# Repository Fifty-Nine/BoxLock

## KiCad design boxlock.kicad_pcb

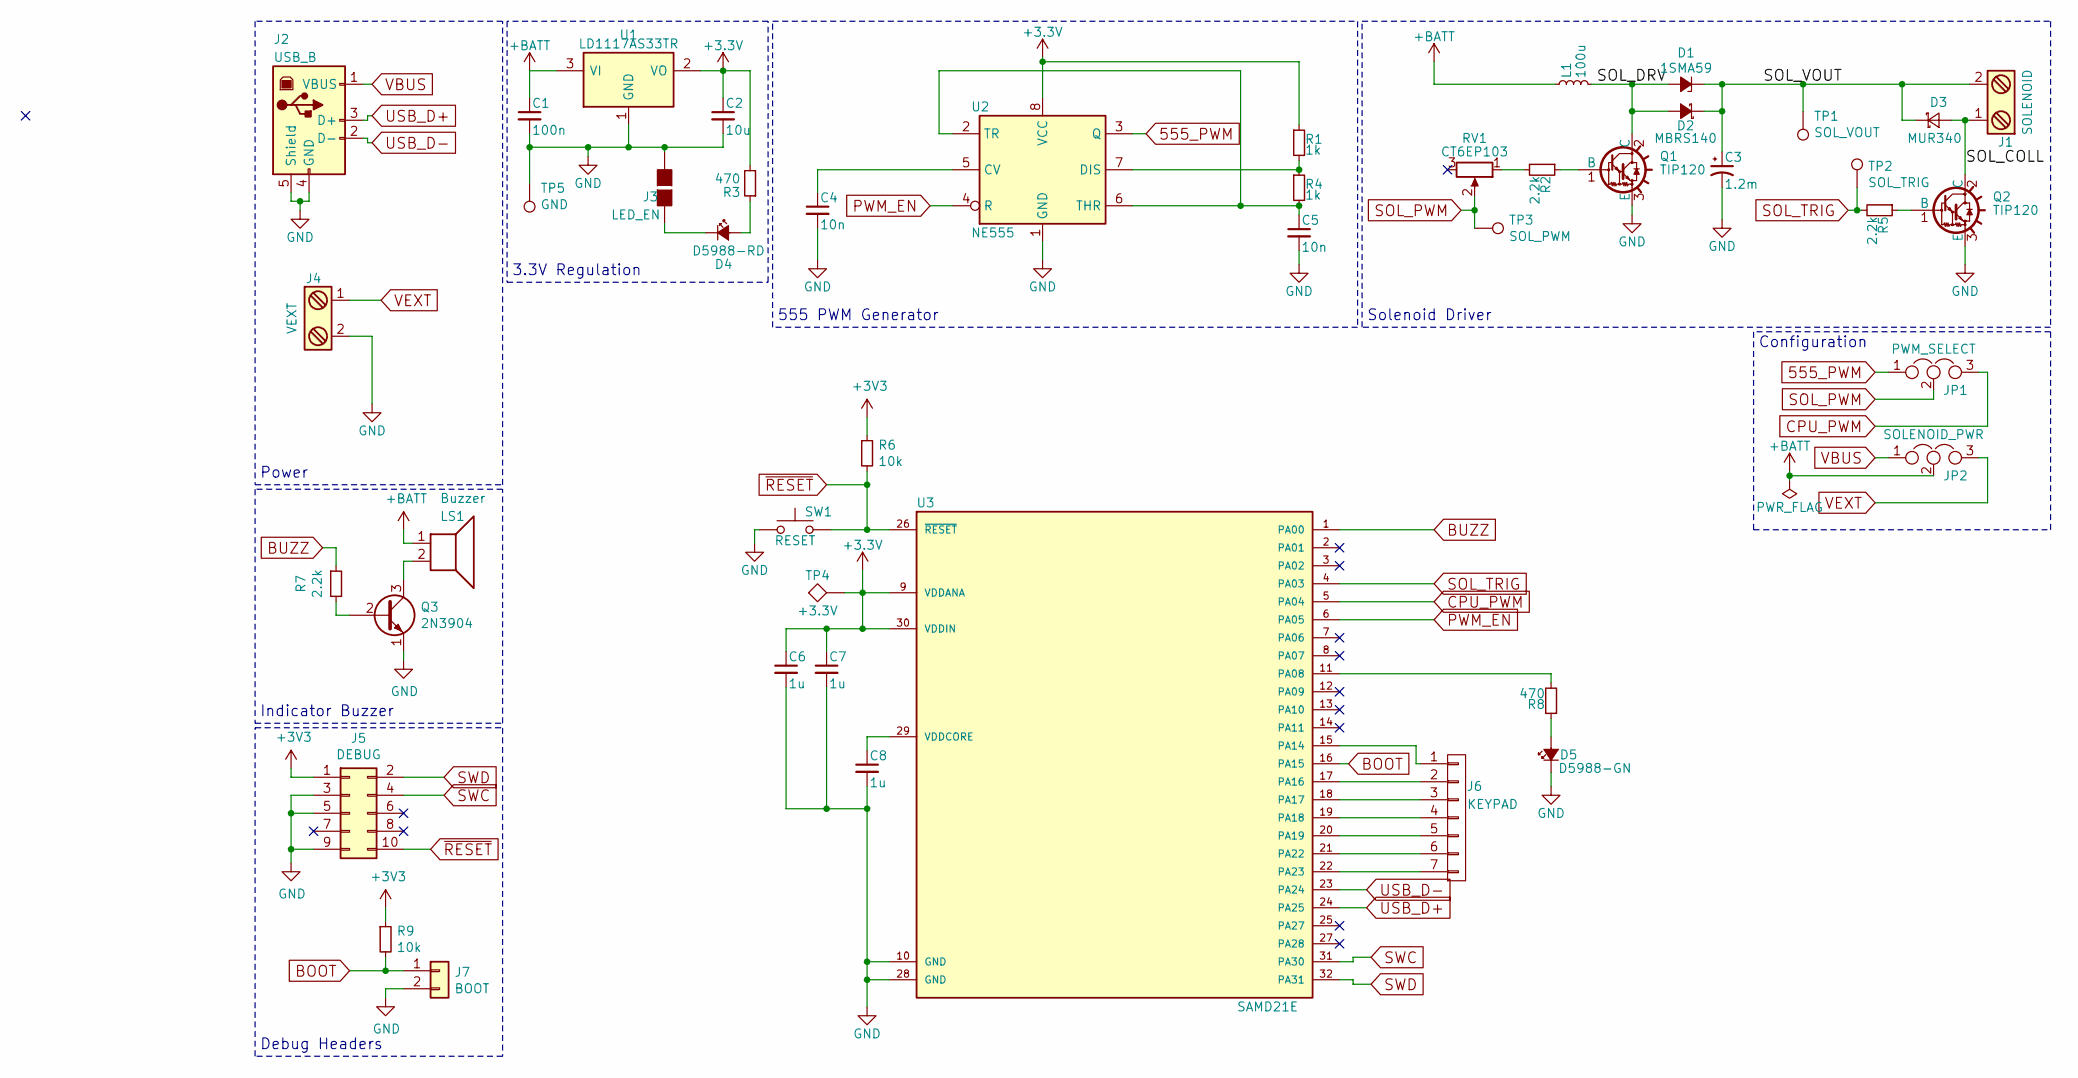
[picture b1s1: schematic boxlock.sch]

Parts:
C1: 100n; C_0805_HandSoldering
C2: 10u; C_0805_HandSoldering
C3: 1.2m; EEV-FK1V152M
C4, C5: 10n; C_0805_HandSoldering
C6, C7, C8: 1u; C_0805_HandSoldering
D1: 1SMA59; D_SMA
D2: MBRS140; D_SMB
D3: MUR340; D_SMB
D4: D5988-RD; LED_0805_HandSoldering
D5: D5988-GN; LED_0805_HandSoldering
J1: SOLENOID; 282836-2
J2: USB_B; USB_Micro-B-circular
J3: LED_EN; GS2
J4: VEXT; 282836-2
J5: DEBUG; Pin_Header_Straight_2x05_Pitch1.27mm
J6: KEYPAD; Pin_Header_Straight_1x07_Pitch2.54mm
J7: BOOT; Pin_Header_Straight_1x02_Pitch2.54mm
JP1: PWM_SELECT; Pin_Header_Straight_1x03_Pitch2.54mm
JP2: SOLENOID_PWR; Pin_Header_Straight_1x03_Pitch2.54mm
L1: 100u; SRN1060-101M
LS1: Buzzer; CEP-2242
Q1, Q2: TIP120; TO-220-3_Horizontal
Q3: 2N3904; TO-92_Molded_Narrow
R1, R4: 1k; R_0805_HandSoldering
R2, R5, R7: 2.2k; R_0805_HandSoldering
R3, R8: 470; R_0805_HandSoldering
R6, R9: 10k; R_0805_HandSoldering
RV1: CT6EP103; 3362P-1-103LF
SW1: RESET; FSMSMTR
TP1: SOL_VOUT; Test_Point_Keystone_5005-5009_Compact
TP2: SOL_TRIG; Test_Point_Keystone_5005-5009_Compact
TP3: SOL_PWM; Test_Point_Keystone_5005-5009_Compact
TP4: +3.3V; Test_Point_Keystone_5005-5009_Compact
TP5: GND; Test_Point_Keystone_5005-5009_Compact
U1: LD1117AS33TR; SOT-223
U2: NE555; SOIC-8_3.9x4.9mm_Pitch1.27mm
U3: SAMD21E; TQFP-32_7x7mm_Pitch0.8mm

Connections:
555_PWM: JP1.1, U2.3 (Q)
+BATT: C1.1, JP2.2, L1.1, LS1.1, U1.3 (VI)
/SOL_COLL: D3.2 (A), J1.1, Q2.2 (C)
/SOL_DRV: D1.2 (A), D2.2 (A), L1.2, Q1.2 (C)
/SOL_VOUT: C3.1, D1.1 (K), D2.1 (K), D3.1 (K), J1.2, TP1.1
BOOT: J7.1, R9.2, U3.16 (PA15)
BUZZ: R7.1, U3.1 (PA00)
CPU_PWM: JP1.3, U3.5 (PA04)
GND: C1.2, C2.2, C3.2, C4.2, C5.2, C6.2, C7.2, C8.2, D5.1 (K), J2.4 (GND), J2.5 (Shield), J3.2 (G2), J4.2, J5.3, J5.5, J5.9, J7.2, Q1.3 (E), Q2.3 (E), Q3.1 (E), SW1.1, TP5.1, U1.1 (GND), U2.1 (GND), U3.10 (GND), U3.28 (GND)
unnamed: C4.1, U2.5 (CV)
unnamed: C5.1, R4.2, U2.2 (TR), U2.6 (THR)
unnamed: C8.1, U3.29 (VDDCORE)
unnamed: D4.1 (K), J3.1 (G1)
unnamed: D4.2 (A), R3.1
unnamed: D5.2 (A), R8.1
unnamed: J6.1, U3.15 (PA14)
unnamed: J6.2, U3.17 (PA16)
unnamed: J6.3, U3.18 (PA17)
unnamed: J6.4, U3.19 (PA18)
unnamed: J6.5, U3.20 (PA19)
unnamed: J6.6, U3.21 (PA22)
unnamed: J6.7, U3.22 (PA23)
unnamed: LS1.2, Q3.3 (C)
unnamed: Q1.1 (B), R2.1
unnamed: Q2.1 (B), R5.1
unnamed: Q3.2 (B), R7.2
unnamed: R1.2, R4.1, U2.7 (DIS)
unnamed: R2.2, RV1.1
unnamed: R8.2, U3.11 (PA08)
PWM_EN: U2.4 (R), U3.6 (PA05)
SOL_PWM: JP1.2, RV1.2, TP3.1
SOL_TRIG: R5.2, TP2.1, U3.4 (PA03)
SWC: J5.4, U3.31 (PA30)
SWD: J5.2, U3.32 (PA31)
USB_D+: J2.3 (D+), U3.24 (PA25)
USB_D-: J2.2 (D-), U3.23 (PA24)
VBUS: J2.1 (VBUS), JP2.1
VEXT: J4.1, JP2.3
~RESET: J5.10, R6.2, SW1.2, U3.26 (~RESET~)

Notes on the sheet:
Solenoid Driver
555 PWM Generator
3.3V Regulation
Configuration
Power
Indicator Buzzer
Debug Headers

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
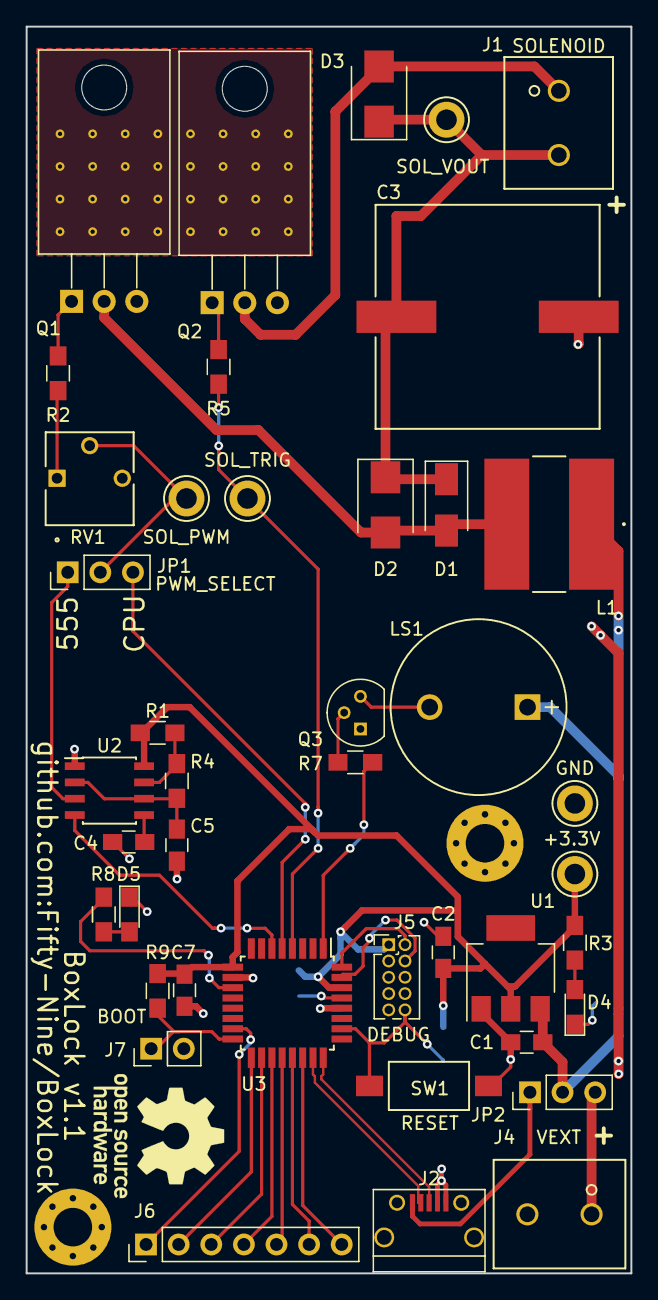
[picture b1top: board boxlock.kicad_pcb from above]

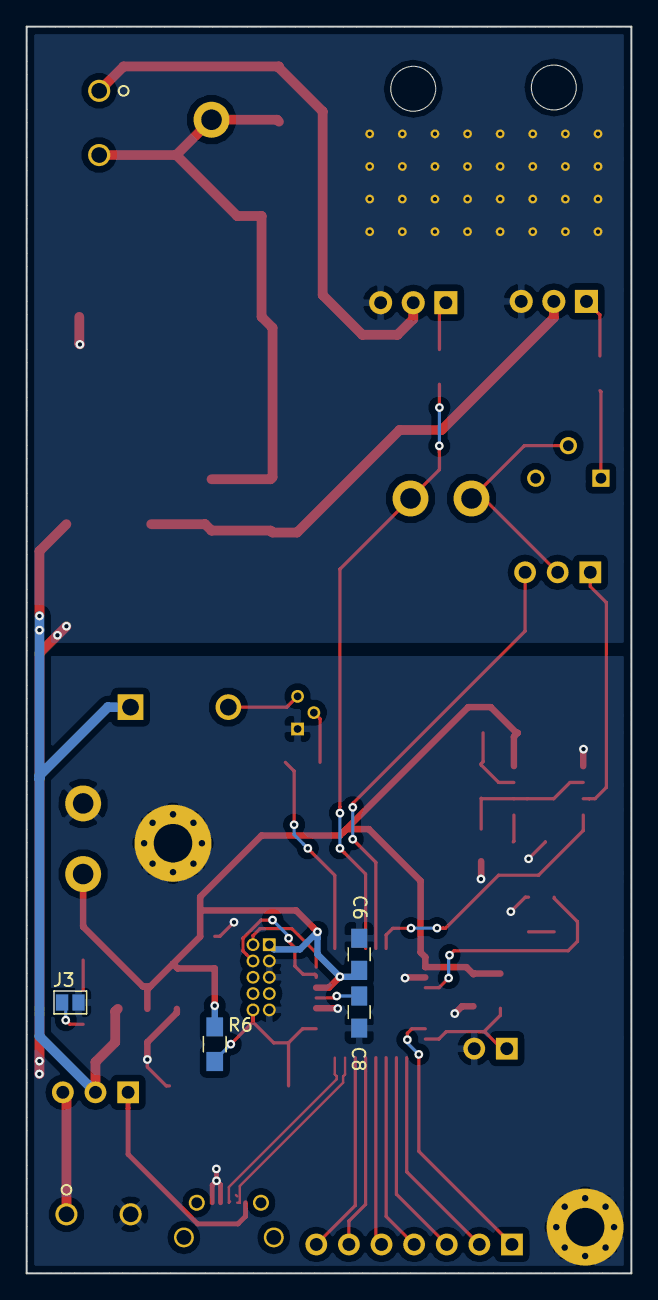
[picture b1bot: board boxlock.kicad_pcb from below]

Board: 2 copper layers, 47.1 x 97.1 mm, 46 parts (4 on the bottom side), 40 nets.

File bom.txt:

Digi-Key Part Number	Quantity	Designation	Package	Customer Reference
478-1395-1-ND	1	100n	C_0805_HandSoldering	C1
478-10568-1-ND	1	10u	C_0805_HandSoldering	C2
478-10447-1-ND	2	10n	C_0805_HandSoldering	"C4,C5"
478-1405-1-ND	3	1u	C_0805_HandSoldering	"C6,C7,C8"
1SMA5927BT3GOSCT-ND	1	1SMA59	D_SMA	D1
MBRS140FSCT-ND	1	MBRS140	D_SMB	D2
MUR340SB R5GCT-ND	1	MUR340	D_SMB	D3
350-2900-ND	2	D5988	LED_0805_HandSoldering	"D4,D5"
A98076-ND	1	SOLENOID	282836-2	J2
609-4618-1-ND	1	USB_B	USB_Micro-B	J3
A98076-ND	1	VEXT	282836-2	J4
TIP120TUFS-ND	2	TIP120	TO-220-3_Horizontal	"Q1,Q2"
P16954CT-ND	2	1k	R_0805_HandSoldering	"R1,R4"
P470ADCT-ND	2	470	R_0805_HandSoldering	"R2,R6"
P2.2KADCT-ND	2	2.2k	R_0805_HandSoldering	"R3,R5"
36-5121-ND	1	555_PWM	Test_Point_Keystone_5005-5009_Compact	TP1
36-5009-ND	1	VSOL	Test_Point_Keystone_5005-5009_Compact	TP2
36-5121-ND	1	CPU_PWM	Test_Point_Keystone_5005-5009_Compact	TP3
497-1228-1-ND	1	LD1117AS33TR	SOT-223	U1
ICM7555IBAZ-TCT-ND	1	NE555	SOIC-8_3.9x4.9mm_Pitch1.27mm	U2
ATMEGA328-AURCT-ND	1	SAMD21E	TQFP-32_7x7mm_Pitch0.8mm	U3
36-5005-ND	1	+3.3V	Test_Point_Keystone_5005-5009_Compact	TP4
SRN1060-101MCT-ND	1	100u	SRN1060-101M	L1
450-1758-1-ND	1	RESET	FSMSMTR	SW1
PCE3466CT-ND	1	1.2m	EEV-FK1V152M	C3
3362P-103LF-ND	1	CT6EP103	3362P-1-103LF	RV1

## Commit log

2017-11-16 Initial commit.
2017-11-18 Relayout for rev 1.1.
2017-11-20 Add license.
2020-08-29 Update to KiCAD 5.0.

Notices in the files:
parts and their libraries:
Copyright 2016 Accelerated Designs. All rights reserved.
